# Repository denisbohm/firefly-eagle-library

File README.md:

firefly-eagle-library
=====================

Firefly Eagle Library

See http://fireflydesign.com for information on the open source Firefly Activity Monitor.

Copyright and License
---------------------
Copyright 2013-2014 Firefly Design LLC / Denis Bohm

<br />This work is licensed under a <a rel="license" href="http://creativecommons.org/licenses/by/3.0/deed.en_US">Creative Commons Attribution 3.0 Unported License</a>.

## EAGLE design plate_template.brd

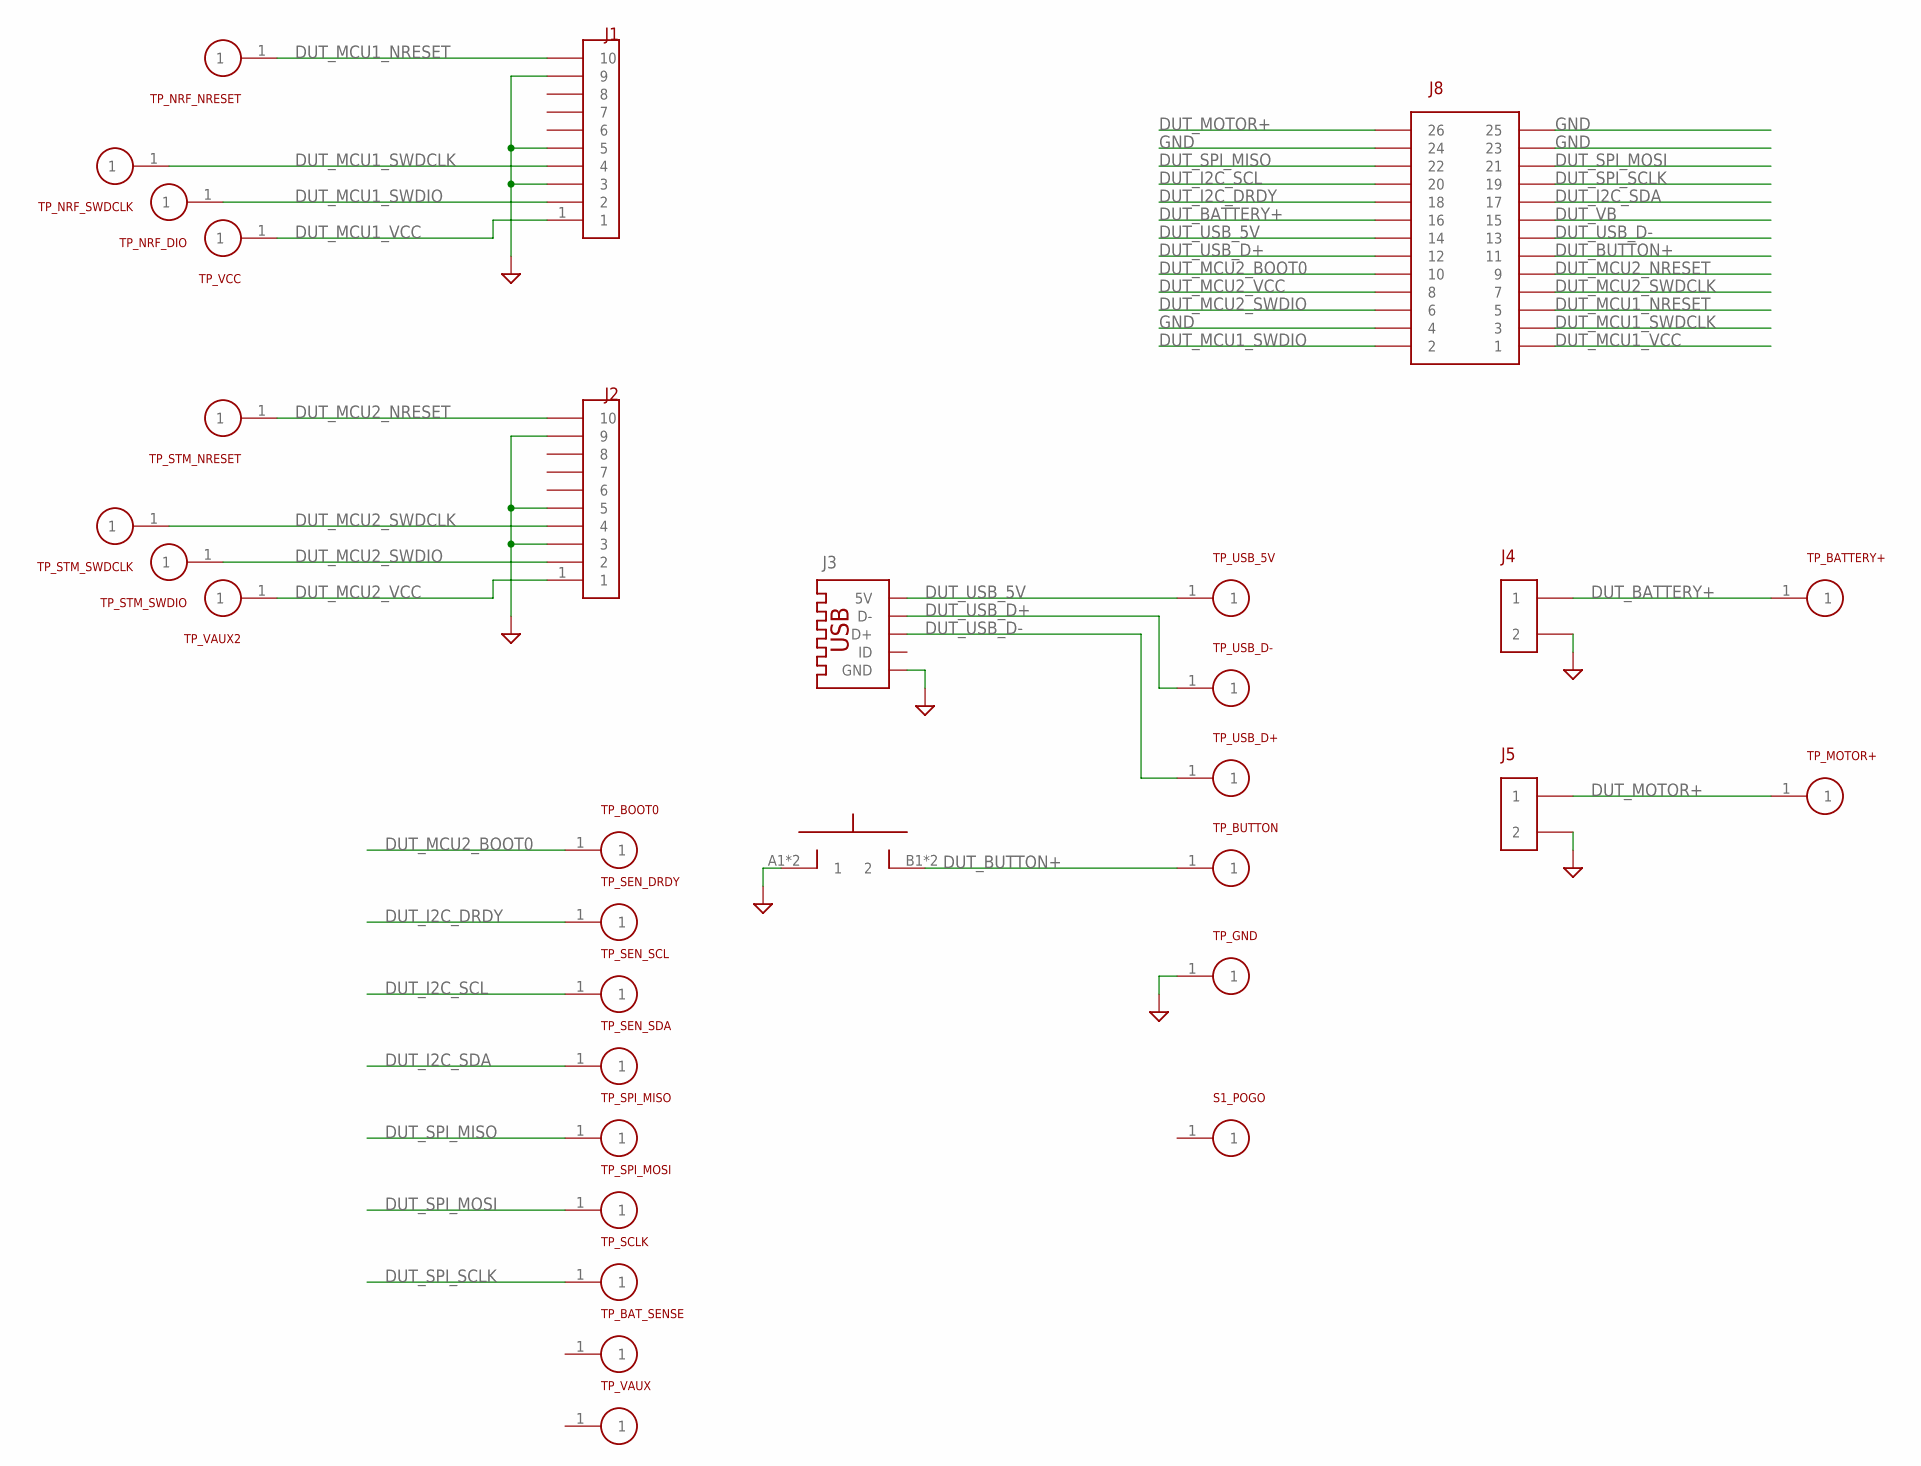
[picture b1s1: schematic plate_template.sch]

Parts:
J1, J2: CON-10SWD; SWD-10
J3: USB-5PIN10118193; 10118193
J4, J5: CON-2CON-HEADER-2; CON-HEADER-2
J8: CON-26; CON-HEADER-2X13
S1: SPST-NORACON8; RACON8
S1_POGO: TARGET-PINPROBE-0985; PROBE-0985
TP_BATTERY+: TARGET-PINPROBE-0985; PROBE-0985
TP_BAT_SENSE: TARGET-PINPROBE-0985; PROBE-0985
TP_BOOT0: TARGET-PINPROBE-0985; PROBE-0985
TP_BUTTON: TARGET-PINPROBE-0985; PROBE-0985
TP_GND: TARGET-PINPROBE-0985; PROBE-0985
TP_MOTOR+: TARGET-PINPROBE-0985; PROBE-0985
TP_NRF_DIO: TARGET-PINPROBE-0985; PROBE-0985
TP_NRF_NRESET: TARGET-PINPROBE-0985; PROBE-0985
TP_NRF_SWDCLK: TARGET-PINPROBE-0985; PROBE-0985
TP_SCLK: TARGET-PINPROBE-0985; PROBE-0985
TP_SEN_DRDY: TARGET-PINPROBE-0985; PROBE-0985
TP_SEN_SCL: TARGET-PINPROBE-0985; PROBE-0985
TP_SEN_SDA: TARGET-PINPROBE-0985; PROBE-0985
TP_SPI_MISO: TARGET-PINPROBE-0985; PROBE-0985
TP_SPI_MOSI: TARGET-PINPROBE-0985; PROBE-0985
TP_STM_NRESET: TARGET-PINPROBE-0985; PROBE-0985
TP_STM_SWDCLK: TARGET-PINPROBE-0985; PROBE-0985
TP_STM_SWDIO: TARGET-PINPROBE-0985; PROBE-0985
TP_USB_5V: TARGET-PINPROBE-0985; PROBE-0985
TP_USB_D+: TARGET-PINPROBE-0985; PROBE-0985
TP_USB_D-: TARGET-PINPROBE-0985; PROBE-0985
TP_VAUX, TP_VAUX2: TARGET-PINPROBE-0985; PROBE-0985
TP_VCC: TARGET-PINPROBE-0985; PROBE-0985

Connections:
DUT_BATTERY+: J4.1, J8.16, TP_BATTERY+.1
DUT_BUTTON+: J8.11, S1.B1 (2), S1.B2 (2), TP_BUTTON.1
DUT_I2C_DRDY: J8.18, TP_SEN_DRDY.1
DUT_I2C_SCL: J8.20, TP_SEN_SCL.1
DUT_I2C_SDA: J8.17, TP_SEN_SDA.1
DUT_MCU1_NRESET: J1.10, J8.5, TP_NRF_NRESET.1
DUT_MCU1_SWDCLK: J1.4, J8.3, TP_NRF_SWDCLK.1
DUT_MCU1_SWDIO: J1.2, J8.2, TP_NRF_DIO.1
DUT_MCU1_VCC: J1.1, J8.1, TP_VCC.1
DUT_MCU2_BOOT0: J8.10, TP_BOOT0.1
DUT_MCU2_NRESET: J2.10, J8.9, TP_STM_NRESET.1
DUT_MCU2_SWDCLK: J2.4, J8.7, TP_STM_SWDCLK.1
DUT_MCU2_SWDIO: J2.2, J8.6, TP_STM_SWDIO.1
DUT_MCU2_VCC: J2.1, J8.8, TP_VAUX2.1
DUT_MOTOR+: J5.1, J8.26, TP_MOTOR+.1
DUT_SPI_MISO: J8.22, TP_SPI_MISO.1
DUT_SPI_MOSI: J8.21, TP_SPI_MOSI.1
DUT_SPI_SCLK: J8.19, TP_SCLK.1
DUT_USB_5V: J3.1 (5V), J8.14, TP_USB_5V.1
DUT_USB_D+: J3.2 (D-), J8.12, TP_USB_D-.1
DUT_USB_D-: J3.3 (D+), J8.13, TP_USB_D+.1
DUT_VB: J8.15
GND: J1.3, J1.5, J1.9, J2.3, J2.5, J2.9, J3.5 (GND), J4.2, J5.2, J8.4, J8.23, J8.24, J8.25, S1.A1 (1), S1.A2 (1), TP_GND.1

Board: 2 copper layers, 32 parts (0 on the bottom side), 22 nets, no tracks yet.

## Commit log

2013-03-22 initial version
2013-03-23 update URL
2013-03-24 update description
2013-06-01 add symbols for firefly ice blue design
2013-06-04 switch P channel source & drain locations for mosfet-n+p
2013-07-13 redimension small capactiors and resistors to Vishay suggested footprints; add more parts; misc fixes & tweaks to existing components
2013-07-29 change R/B labels on LED to match actual layout (pins numbers are reflected)
2013-09-03 add part name on top documentation layer
2013-09-10 move some name to document layer
2014-02-05 add test fixture components
2014-02-05 update license date
2014-02-28 add waterproof connector
2015-08-19 new footprints
2015-12-01 some cleanup and new packages
2016-05-04 add FRDM-K22F
2016-06-01 rev 0.2 of instrument board
2016-11-21 snowflake parts
2017-01-24 start of template for test fixture adapter board
2017-01-24 add cutout for header pins
2017-06-28 plate updates
